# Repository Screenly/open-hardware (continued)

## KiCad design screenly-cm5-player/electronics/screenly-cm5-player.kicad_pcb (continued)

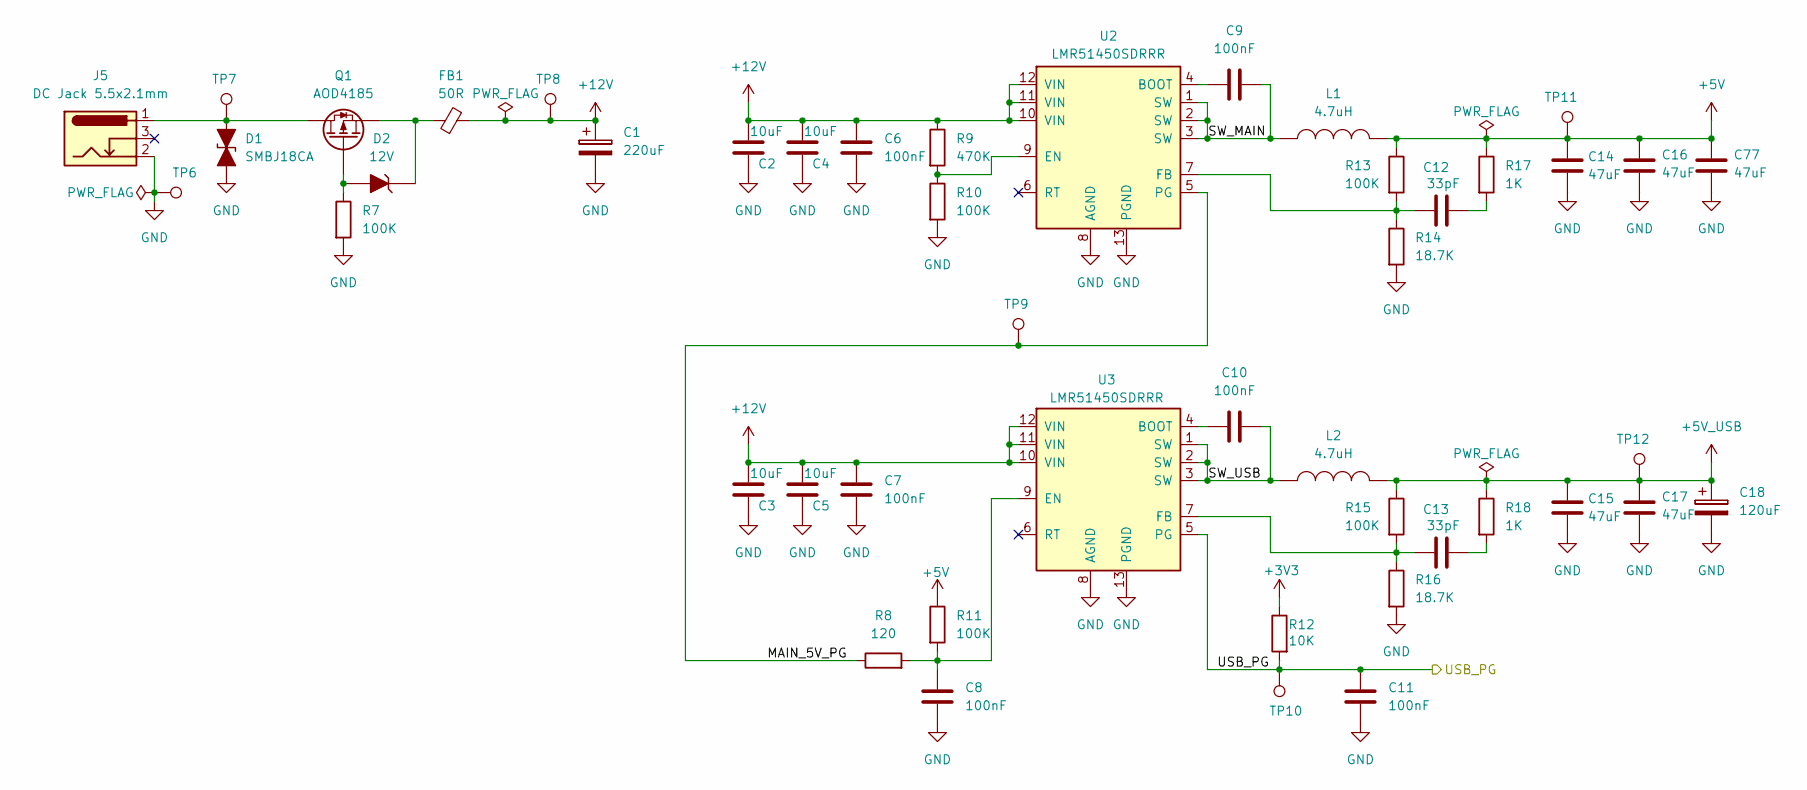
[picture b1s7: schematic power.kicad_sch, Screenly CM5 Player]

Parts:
C1: 220uF; CP_Radial_D6.3mm_P2.50mm; tolerance 20%; voltage 35V; PartNumber SRLY-CAP-000008
C2, C3, C4, C5: 10uF; C_1210; tolerance 10%; voltage 50V; PartNumber SRLY-CAP-000002
C6, C7, C8, C9, C10, C11: 100nF; C_0402; tolerance 10%; voltage 50V; PartNumber SRLY-CAP-000001
C12, C13: 33pF; C_0402; tolerance 5%; voltage 50V; PartNumber SRLY-CAP-000003
C14, C15, C16, C17, C77: 47uF; C_1210; tolerance 10%; voltage 10V; PartNumber SRLY-CAP-000005
C18: 120uF; CP_Elec_6.3x5.9; tolerance 20%; voltage 10V; PartNumber SRLY-CAP-000006
D1: SMBJ18CA; D_SMB; PartNumber SRLY-DIO-000001
D2: 12V; D_SOD-123; tolerance 6%; PartNumber SRLY-DIO-000002
FB1: 50R; FB_1206; PartNumber SRLY-FBD-000001
J5: DC Jack 5.5x2.1mm; BarrelJack_Tensility_54-00129_Horizontal; voltage 57V; PartNumber SRLY-CON-000004
L1, L2: 4.7uH; L_Coilank_AAPS1050; tolerance 20%; PartNumber SRLY-IND-000001
Q1: AOD4185; TO-252-2; PartNumber SRLY-FET-000001
R7, R10, R11, R13, R15: 100K; R_0402; tolerance 1%; voltage 50V; PartNumber SRLY-RES-000004
R8: 120; R_0402; tolerance 5%; voltage 50V; PartNumber SRLY-RES-000009
R9: 470K; R_0402; tolerance 5%; voltage 50V; PartNumber SRLY-RES-000003
R12: 10K; R_0402; tolerance 1%; voltage 50V; PartNumber SRLY-RES-000005
R14, R16: 18.7K; R_0402; tolerance 1%; voltage 50V; PartNumber SRLY-RES-000016
R17, R18: 1K; R_0402; tolerance 5%; voltage 50V; PartNumber SRLY-RES-000006
TP6, TP7, TP8, TP9, TP10, TP11, TP12: TestPoint; TestPoint_Pad_D2.0mm
U2, U3: LMR51450SDRRR; TI_WSON-12-1EP_3x3mm_P0.5mm_EP1.3x2.5mm; PartNumber SRLY-PWR-000001

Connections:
+3V3: R12.1; also elsewhere on the board
+5V: C14.1, C16.1, C77.1, L1.2, R11.1, R13.1, R17.1, TP11.1 (1_1); also elsewhere on the board
+5V_USB: C15.1, C17.1, C18.1, L2.2, R15.1, R18.1, TP12.1 (1_1); also elsewhere on the board
+12V: C1.1, C2.1, C3.1, C4.1, C5.1, C6.1, C7.1, FB1.2, R9.1, TP8.1 (1_1), U2.10 (VIN), U2.11 (VIN), U2.12 (VIN), U3.10 (VIN), U3.11 (VIN), U3.12 (VIN); also elsewhere on the board
/Power/MAIN_5V_PG: R8.1, TP9.1 (1_1), U2.5 (PG)
/Power/SW_MAIN: C9.2, L1.1, U2.1 (SW), U2.2 (SW), U2.3 (SW)
/Power/SW_USB: C10.2, L2.1, U3.1 (SW), U3.2 (SW), U3.3 (SW)
/USB_PG: C11.2, R12.2, TP10.1 (1_1), U3.5 (PG); also elsewhere on the board
GND: C1.2, C2.2, C3.2, C4.2, C5.2, C6.2, C7.2, C8.1, C11.1, C14.2, C15.2, C16.2, C17.2, C18.2, C77.2, D1.2 (A2), J5.2, R7.2, R10.2, R14.2, R16.2, TP6.1 (1_1), U2.8 (AGND), U2.13 (PGND), U3.8 (AGND), U3.13 (PGND); also elsewhere on the board
unnamed: C12.2, R17.2
unnamed: C13.2, R18.2
unnamed: D1.1 (A1), J5.1, Q1.2 (D), TP7.1 (1_1)
unnamed: D2.2 (A), Q1.1 (G), R7.1
unnamed: D2.1 (K), FB1.1, Q1.3 (S)
unnamed: C9.1, U2.4 (BOOT)
unnamed: R9.2, R10.1, U2.9 (EN)
unnamed: C12.1, R13.2, R14.1, U2.7 (FB)
unnamed: C10.1, U3.4 (BOOT)
unnamed: C8.2, R8.2, R11.2, U3.9 (EN)
unnamed: C13.1, R15.2, R16.1, U3.7 (FB)

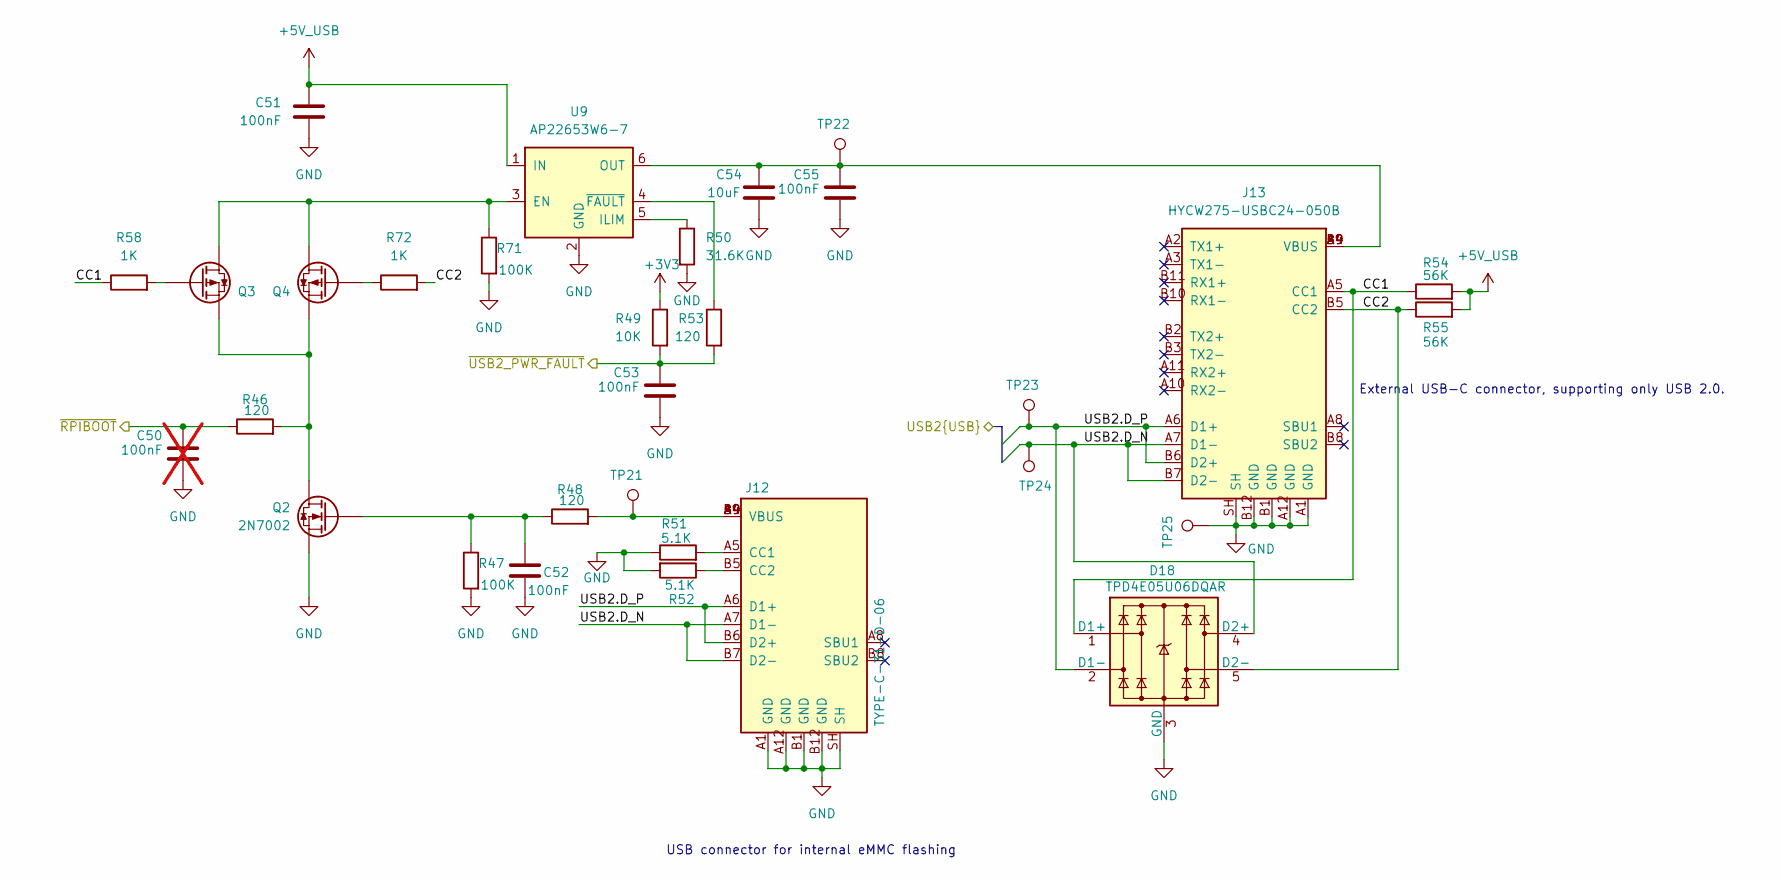
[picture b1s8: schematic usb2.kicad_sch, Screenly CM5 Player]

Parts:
C50: 100nF; C_0402; tolerance 10%; voltage 50V; PartNumber SRLY-CAP-000001; not fitted
C51, C52, C53, C55: 100nF; C_0402; tolerance 10%; voltage 50V; PartNumber SRLY-CAP-000001
C54: 10uF; C_1210; tolerance 10%; voltage 50V; PartNumber SRLY-CAP-000002
D18: TPD4E05U06DQAR; TI_USON-10_2.5x1.0mm_P0.5mm; PartNumber SRLY-DIO-000004
J12: TYPE-C-31-D-06; USB_C_Receptacle_HRO_TYPE-C-31-D-06_Vertical; voltage 5V; PartNumber SRLY-CON-000010
J13: HYCW275-USBC24-050B; USB_C_Receptacle_HOAUC_HYCW275-USBC24-050B; PartNumber SRLY-CON-000009
Q2: 2N7002; SOT-23; PartNumber SRLY-FET-000002
Q3, Q4: AO3401A; SOT-23; PartNumber SRLY-FET-000003
R46, R48, R53: 120; R_0402; tolerance 5%; voltage 50V; PartNumber SRLY-RES-000009
R47, R71: 100K; R_0402; tolerance 1%; voltage 50V; PartNumber SRLY-RES-000004
R49: 10K; R_0402; tolerance 1%; voltage 50V; PartNumber SRLY-RES-000005
R50: 31.6K; R_0402; tolerance 1%; voltage 50V; PartNumber SRLY-RES-000010
R51, R52: 5.1K; R_0402; tolerance 1%; voltage 50V; PartNumber SRLY-RES-000012
R54, R55: 56K; R_0402; tolerance 1%; voltage 50V; PartNumber SRLY-RES-000013
R58, R72: 1K; R_0402; tolerance 5%; voltage 50V; PartNumber SRLY-RES-000006
TP21, TP22, TP23, TP24, TP25: TestPoint; TestPoint_Pad_D2.0mm
U9: AP22653W6-7; SOT-23-6; PartNumber SRLY-PWR-000003

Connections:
+3V3: R49.1; also elsewhere on the board
+5V_USB: C51.1, R54.2, R55.2, U9.1 (IN); also elsewhere on the board
/Compute Module/USB2.D_N: D18.4 (D2+), D18.7, J12.A7 (D1-), J12.B7 (D2-), J13.A7 (D1-), J13.B7 (D2-), TP24.1 (1_1); also elsewhere on the board
/Compute Module/USB2.D_P: D18.2 (D1-), D18.9, J12.A6 (D1+), J12.B6 (D2+), J13.A6 (D1+), J13.B6 (D2+), TP23.1 (1_1); also elsewhere on the board
/Compute Module/~RPIBOOT: C50.1, R46.1; also elsewhere on the board
/Compute Module/~USB2_PWR_FAULT: C53.1, R49.2, R53.2; also elsewhere on the board
/USB2/CC1: D18.1 (D1+), D18.10, J13.A5 (CC1), R54.1, R58.1
/USB2/CC2: D18.5 (D2-), D18.6, J13.B5 (CC2), R55.1, R72.2
GND: C50.2, C51.2, C52.2, C53.2, C54.2, C55.2, D18.3 (GND), D18.8 (GND), J12.A1 (GND), J12.A12 (GND), J12.B1 (GND), J12.B12 (GND), J12.SH, J13.A1 (GND), J13.A12 (GND), J13.B1 (GND), J13.B12 (GND), J13.SH, Q2.2 (S), R47.2, R50.2, R51.1, R52.2, R71.2, TP25.1 (1_1), U9.2 (GND); also elsewhere on the board
unnamed: J12.A5 (CC1), R51.2
unnamed: J12.B5 (CC2), R52.1
unnamed: J12.A4 (VBUS), J12.A9 (VBUS), J12.B4 (VBUS), J12.B9 (VBUS), R48.2, TP21.1 (1_1)
unnamed: Q2.3 (D), Q3.2 (S), Q4.2 (S), R46.2
unnamed: C52.1, Q2.1 (G), R47.1, R48.1
unnamed: Q3.3 (D), Q4.3 (D), R71.1, U9.3 (EN)
unnamed: Q3.1 (G), R58.2
unnamed: Q4.1 (G), R72.1
unnamed: R50.1, U9.5 (ILIM)
unnamed: C54.1, C55.1, J13.A4 (VBUS), J13.A9 (VBUS), J13.B4 (VBUS), J13.B9 (VBUS), TP22.1 (1_1), U9.6 (OUT)
unnamed: R53.1, U9.4 (~FAULT)

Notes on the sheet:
External USB-C connector, supporting only USB 2.0.
USB connector for internal eMMC flashing

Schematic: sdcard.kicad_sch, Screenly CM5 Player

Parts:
C60, C61: 100nF; C_0402; tolerance 10%; voltage 50V; PartNumber SRLY-CAP-000001
C62: 10uF; C_1210; tolerance 10%; voltage 50V; PartNumber SRLY-CAP-000002
J14: 0472192001; microSD_HC_Molex_47219-2001; PartNumber SRLY-CON-000012
R62: 120; R_0402; tolerance 10%; voltage 50V; PartNumber SRLY-RES-000009
R63: 10K; R_0402; tolerance 1%; voltage 50V; PartNumber SRLY-RES-000005
R64: 47K; R_0402; tolerance 1%; voltage 50V; PartNumber SRLY-RES-000015
TP26: TestPoint; TestPoint_Pad_D2.0mm
U11: AP22653W6-7; SOT-23-6; PartNumber SRLY-PWR-000003

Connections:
+3V3: C60.1, R63.1, U11.1 (IN); also elsewhere on the board
/Compute Module/SD_CARD.CLK: J14.5 (CLK); also elsewhere on the board
/Compute Module/SD_CARD.CMD: J14.3 (CMD); also elsewhere on the board
/Compute Module/SD_CARD.D0: J14.7 (DAT0); also elsewhere on the board
/Compute Module/SD_CARD.D1: J14.8 (DAT1); also elsewhere on the board
/Compute Module/SD_CARD.D2: J14.1 (DAT2); also elsewhere on the board
/Compute Module/SD_CARD.D3: J14.2 (DAT3/CD); also elsewhere on the board
/Compute Module/SD_CARD.PWR_ON: R62.1; also elsewhere on the board
GND: C60.2, C61.2, C62.2, J14.6 (VSS), J14.SH, R64.2, U11.2 (GND); also elsewhere on the board
unnamed: C61.1, C62.1, J14.4 (VDD), TP26.1 (1_1), U11.6 (OUT)
unnamed: R62.2, R63.2, U11.3 (EN)
unnamed: R64.1, U11.5 (ILIM)

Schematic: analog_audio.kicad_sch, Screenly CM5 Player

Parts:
C64, C69, C70, C73: 100nF; C_0402; tolerance 10%; voltage 50V; PartNumber SRLY-CAP-000001
C65, C66, C67, C68: 10uF; C_1210; tolerance 10%; voltage 50V; PartNumber SRLY-CAP-000002
C71, C72: 2.2uF; C_0603; tolerance 10%; voltage 16V; PartNumber SRLY-CAP-000009
C74, C75: 2.2nF; C_0402; tolerance 5%; voltage 50V; PartNumber SRLY-CAP-000010
D17: PESD5V0U2BT; SOT-23; PartNumber SRLY-DIO-000005
J15: PJ-320A-4P; Jack_3.5mm_SHOUHAN_PJ-320A-4P_Horizontal; voltage 30V; PartNumber SRLY-CON-000013
R68: 10K; R_0402; tolerance 1%; voltage 50V; PartNumber SRLY-RES-000005
R69, R70: 470; R_0402; tolerance 5%; voltage 50V; PartNumber SRLY-RES-000001
U13: PCM5102APWR; TSSOP-20_4.4x6.5mm_P0.65mm; PartNumber SRLY-ITC-000003

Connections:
+3V3: C64.1, C65.1, C66.1, C68.1, C69.1, C73.1, R68.1, U13.1 (CPVDD), U13.8 (AVDD), U13.20 (DVDD); also elsewhere on the board
/Analog Audio/Audio.SCLK: U13.13 (BCK); also elsewhere on the board
/Analog Audio/Audio.SDO0: U13.14 (DIN); also elsewhere on the board
/Analog Audio/Audio.WS: U13.15 (LRCK); also elsewhere on the board
GND: C64.2, C65.2, C66.2, C67.2, C68.2, C69.2, C70.2, C72.2, C73.2, C74.1, C75.2, D17.3 (GND), J15.A (S), J15.B (R2), U13.3 (CPGND), U13.9 (AGND), U13.10 (DEMP), U13.11 (FLT), U13.12 (SCK), U13.16 (FMT), U13.19 (DGND); also elsewhere on the board
unnamed: C74.2, D17.1 (IO1), J15.D (T), R69.2
unnamed: C75.1, D17.2 (IO2), J15.C (R1), R70.2
unnamed: C71.2, U13.4 (CAPM)
unnamed: C71.1, U13.2 (CAPP)
unnamed: C67.1, C70.1, U13.18 (LDOO)
unnamed: R69.1, U13.6 (OUTL)
unnamed: R70.1, U13.7 (OUTR)
unnamed: C72.1, U13.5 (VNEG)
unnamed: R68.2, U13.17 (XSMT)

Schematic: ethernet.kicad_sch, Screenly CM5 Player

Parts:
C19: 100nF; C_0402; tolerance 10%; voltage 50V; PartNumber SRLY-CAP-000001
D3, D4: TPD4E05U06DQAR; TI_USON-10_2.5x1.0mm_P0.5mm; PartNumber SRLY-DIO-000004
J6: HB-W01G0520DQW-R; RJ45_Hanbo_HB-W01G0520DQW-R_Horizontal; PartNumber SRLY-CON-000005
R19, R20: 470; R_0402; tolerance 5%; voltage 50V; PartNumber SRLY-RES-000001

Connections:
+3V3: J6.L1 (LED_GRN_A), J6.L4 (LED_YEL_A); also elsewhere on the board
/Compute Module/ETH.TRD0_N: D3.2 (D1-), D3.9, J6.3 (TD1-); also elsewhere on the board
/Compute Module/ETH.TRD0_P: D3.1 (D1+), D3.10, J6.2 (TD1+); also elsewhere on the board
/Compute Module/ETH.TRD1_N: D3.4 (D2+), D3.7, J6.7 (TD2-); also elsewhere on the board
/Compute Module/ETH.TRD1_P: D3.5 (D2-), D3.6, J6.4 (TD2+); also elsewhere on the board
/Compute Module/ETH.TRD2_N: D4.2 (D1-), D4.9, J6.6 (TD3-); also elsewhere on the board
/Compute Module/ETH.TRD2_P: D4.1 (D1+), D4.10, J6.5 (TD3+); also elsewhere on the board
/Compute Module/ETH.TRD3_N: D4.4 (D2+), D4.7, J6.9 (TD4-); also elsewhere on the board
/Compute Module/ETH.TRD3_P: D4.5 (D2-), D4.6, J6.8 (TD4+); also elsewhere on the board
/Compute Module/~ETH_LED_ACT: R20.2; also elsewhere on the board
/Compute Module/~ETH_LED_SPD: R19.2; also elsewhere on the board
GND: C19.2, D3.3 (GND), D3.8 (GND), D4.3 (GND), D4.8 (GND), J6.10 (CAP_GND), J6.SH (SHIELD); also elsewhere on the board
unnamed: C19.1, J6.1 (CT)
unnamed: J6.L2 (LED_GRN_K), R20.1
unnamed: J6.L3 (LED_YEL_K), R19.1

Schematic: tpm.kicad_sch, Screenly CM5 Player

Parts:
C56, C57, C58, C76: 100nF; C_0402; tolerance 10%; voltage 50V; PartNumber SRLY-CAP-000001
C59: 1uF; C_0402; tolerance 10%; voltage 25V; PartNumber SRLY-CAP-000007
R56, R57: 10K; R_0402; tolerance 1%; voltage 50V; PartNumber SRLY-RES-000005
R59, R60, R61: 33R; R_0402; tolerance 5%; voltage 50V; PartNumber SRLY-RES-000014
U10: SLB9672XU20FW1624; Infineon_PG-UQFN-32-1_5x5mm_P0.5mm_EP3.6x3.6mm; PartNumber SRLY-ITC-000002

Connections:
+3V3: C56.1, C57.1, C58.1, C59.1, R56.1, R57.1, U10.1 (VDD), U10.8 (NCI/VDD), U10.14 (VDD), U10.22 (VDD); also elsewhere on the board
/Compute Module/TPM.CLK: R59.1; also elsewhere on the board
/Compute Module/TPM.MISO: R61.1; also elsewhere on the board
/Compute Module/TPM.MOSI: R60.1; also elsewhere on the board
/Compute Module/TPM.~CS: R56.2, U10.20 (~CS); also elsewhere on the board
/Compute Module/~TPM_PIRQ: R57.2, U10.18 (~PIRQ); also elsewhere on the board
/Compute Module/~TPM_RST: C76.1, U10.17 (~RST); also elsewhere on the board
/TPM/TPM_CLK_F: R59.2, U10.19 (SCLK)
/TPM/TPM_MISO_F: R61.2, U10.24 (MISO)
/TPM/TPM_MOSI_F: R60.2, U10.21 (MOSI)
GND: C56.2, C57.2, C58.2, C59.2, C76.2, U10.2 (GND), U10.9 (GND), U10.16 (NCI/GND), U10.23 (GND), U10.32 (GND), U10.33 (GND); also elsewhere on the board

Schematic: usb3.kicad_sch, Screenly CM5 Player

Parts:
C38, C39, C40, C41, C42, C43, C46, C47: 100nF; C_0402; tolerance 10%; voltage 50V; PartNumber SRLY-CAP-000001
C44, C45: 10uF; C_1210; tolerance 10%; voltage 50V; PartNumber SRLY-CAP-000002
D11, D12, D13, D14: TPD4E05U06DQAR; TI_USON-10_2.5x1.0mm_P0.5mm; PartNumber SRLY-DIO-000004
J10, J11: USB-A3-S-RA; USB_A_USB3_AdamTech_USB-A3-S-RA_Horizontal; voltage 30V; PartNumber SRLY-CON-000011
R33, R34: 100K; R_0402; tolerance 1%; voltage 50V; PartNumber SRLY-RES-000004
R35, R36, R38: 10K; R_0402; tolerance 1%; voltage 50V; PartNumber SRLY-RES-000005
R37: 18.7K; R_0402; tolerance 1%; voltage 50V; PartNumber SRLY-RES-000016
R39, R40: 120; R_0402; tolerance 5%; voltage 50V; PartNumber SRLY-RES-000009
TP15, TP16: TestPoint; TestPoint_Pad_D2.0mm
U7, U8: AP22653W6-7; SOT-23-6; PartNumber SRLY-PWR-000003

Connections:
+3V3: R35.1, R36.1; also elsewhere on the board
+5V_USB: C38.1, C39.1, U7.1 (IN), U8.1 (IN); also elsewhere on the board
/Compute Module/USB3_0.D_N: D11.2 (D1-), D11.9, J10.2 (D-); also elsewhere on the board
/Compute Module/USB3_0.D_P: D11.1 (D1+), D11.10, J10.3 (D+); also elsewhere on the board
/Compute Module/USB3_0.RX_N: D13.4 (D2+), D13.7, J10.5 (SSRX-); also elsewhere on the board
/Compute Module/USB3_0.RX_P: D13.5 (D2-), D13.6, J10.6 (SSRX+); also elsewhere on the board
/Compute Module/USB3_0.TX_N: D11.4 (D2+), D11.7, J10.8 (SSTX-); also elsewhere on the board
/Compute Module/USB3_0.TX_P: D11.5 (D2-), D11.6, J10.9 (SSTX+); also elsewhere on the board
/Compute Module/USB3_1.D_N: D12.2 (D1-), D12.9, J11.2 (D-); also elsewhere on the board
/Compute Module/USB3_1.D_P: D12.1 (D1+), D12.10, J11.3 (D+); also elsewhere on the board
/Compute Module/USB3_1.RX_N: D14.5 (D2-), D14.6, J11.5 (SSRX-); also elsewhere on the board
/Compute Module/USB3_1.RX_P: D14.4 (D2+), D14.7, J11.6 (SSRX+); also elsewhere on the board
/Compute Module/USB3_1.TX_N: D12.4 (D2+), D12.7, J11.8 (SSTX-); also elsewhere on the board
/Compute Module/USB3_1.TX_P: D12.5 (D2-), D12.6, J11.9 (SSTX+); also elsewhere on the board
/Compute Module/VBUS_EN: C40.1, C41.1, R33.1, R34.1, U7.3 (EN), U8.3 (EN); also elsewhere on the board
/Compute Module/~USB3_0_PWR_FAULT: C42.1, R35.2, R39.2; also elsewhere on the board
/Compute Module/~USB3_1_PWR_FAULT: C43.1, R36.2, R40.2; also elsewhere on the board
GND: C38.2, C39.2, C40.2, C41.2, C42.2, C43.2, C44.2, C45.2, C46.2, C47.2, D11.3 (GND), D11.8 (GND), D12.3 (GND), D12.8 (GND), D13.3 (GND), D13.8 (GND), D14.3 (GND), D14.8 (GND), J10.4 (GND), J10.7 (GND_DRAIN), J10.SH, J11.4 (GND), J11.7 (GND_DRAIN), J11.SH, R33.2, R34.2, R37.2, R38.2, U7.2 (GND), U8.2 (GND); also elsewhere on the board
unnamed: C44.1, C46.1, J10.1 (VBUS), TP15.1 (1_1), U7.6 (OUT)
unnamed: C45.1, C47.1, J11.1 (VBUS), TP16.1 (1_1), U8.6 (OUT)
unnamed: R37.1, U7.5 (ILIM)
unnamed: R39.1, U7.4 (~FAULT)
unnamed: R38.1, U8.5 (ILIM)
unnamed: R40.1, U8.4 (~FAULT)

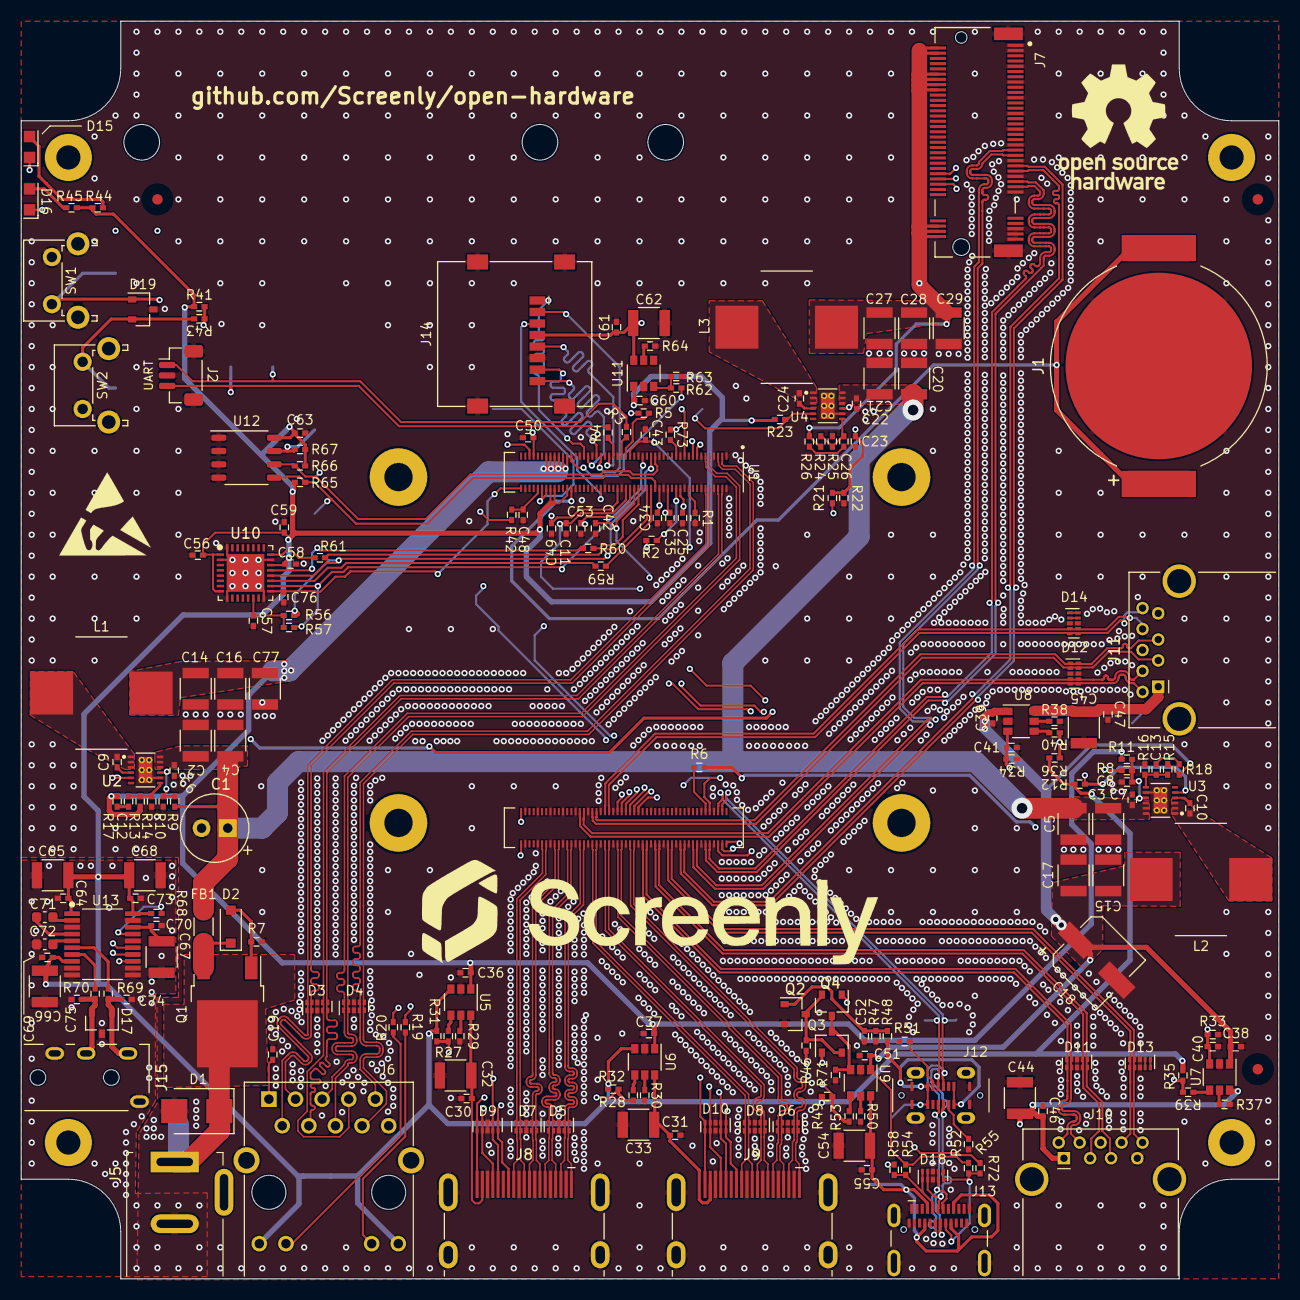
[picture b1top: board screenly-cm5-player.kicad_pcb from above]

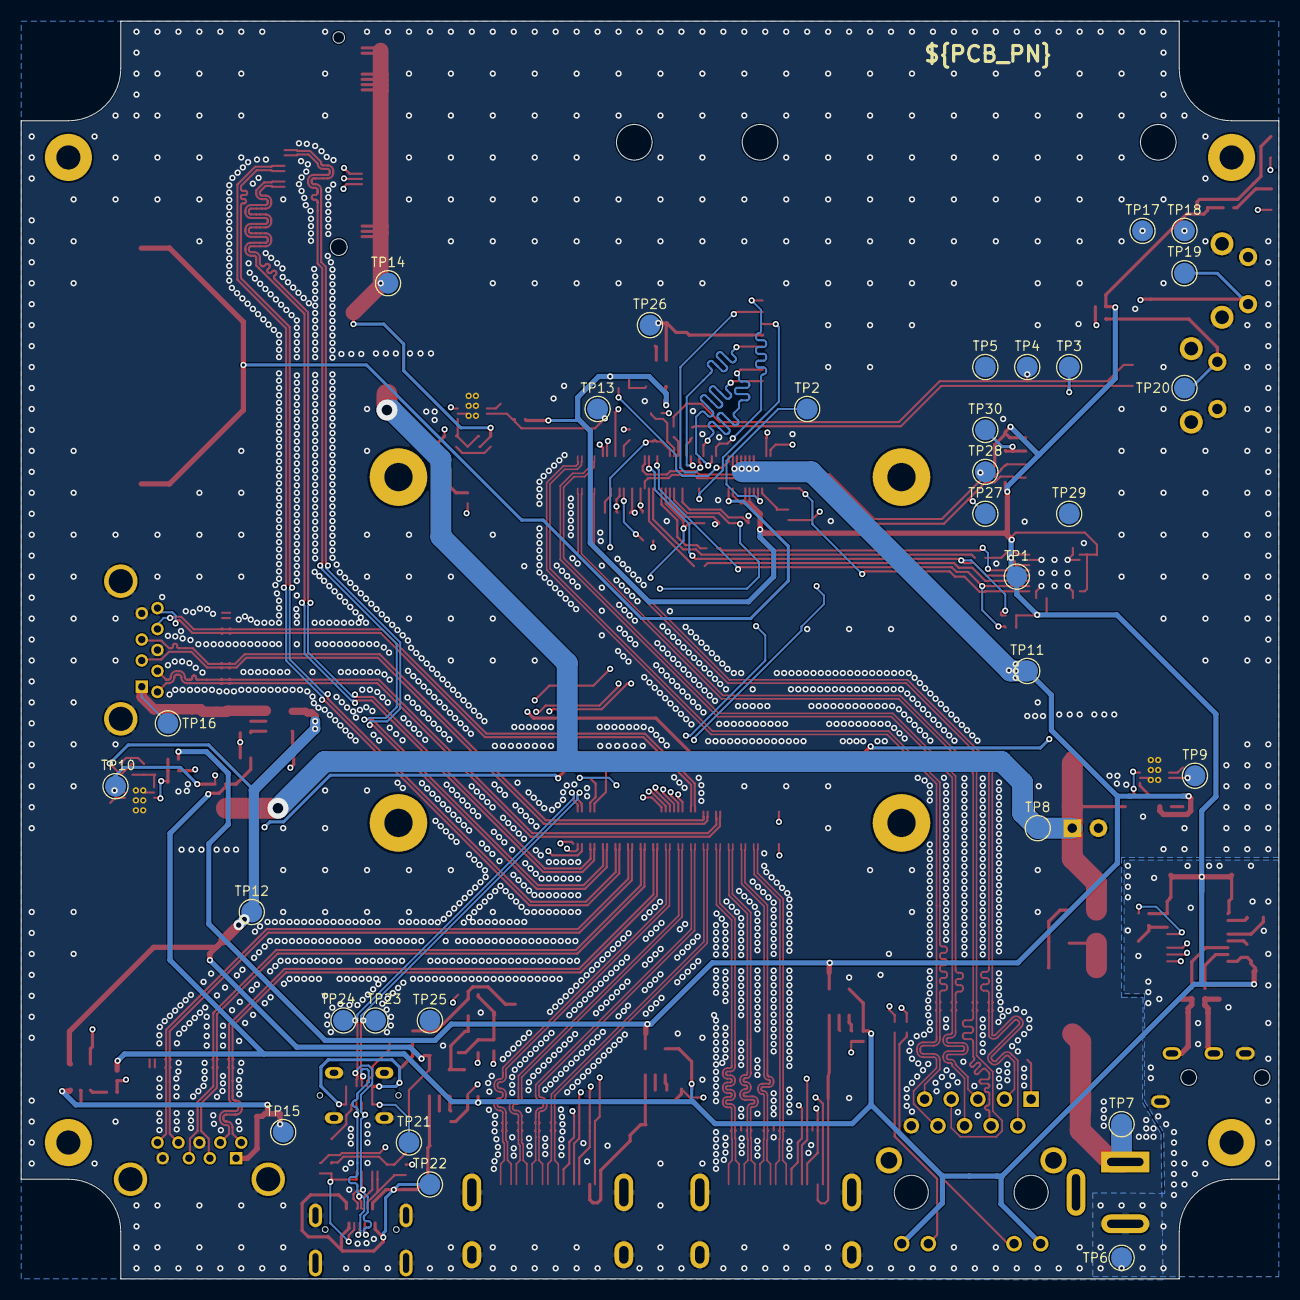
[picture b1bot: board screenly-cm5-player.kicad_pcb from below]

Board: 4 copper layers, 120.0 x 120.0 mm, 248 parts (30 on the bottom side), 173 nets.

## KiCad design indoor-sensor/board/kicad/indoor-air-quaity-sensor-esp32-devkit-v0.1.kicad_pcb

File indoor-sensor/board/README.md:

# Indoor Air Quality Sensor – XIAO ESP32S3 & CJMCU-6668

This repository contains the hardware design files for a compact Indoor Air Quality Sensor based on the Seeed Studio XIAO ESP32S3 and the CJMCU-6668 environmental sensor module (ENS160 + BME280).

## Main Components

| Part | Description |
|------|-------------|
| XIAO ESP32S3 | Primary MCU module (WiFi + BLE) |
| CJMCU-6668 | ENS160 + BME280 environmental sensor |
| I²C Pull-ups | 4.7kΩ resistors (if required) |
| Connector Headers | XIAO pin headers, sensor headers |
| Power Supply | USB-C (via XIAO) |
| Mounting Hardware | Optional standoffs and enclosure |

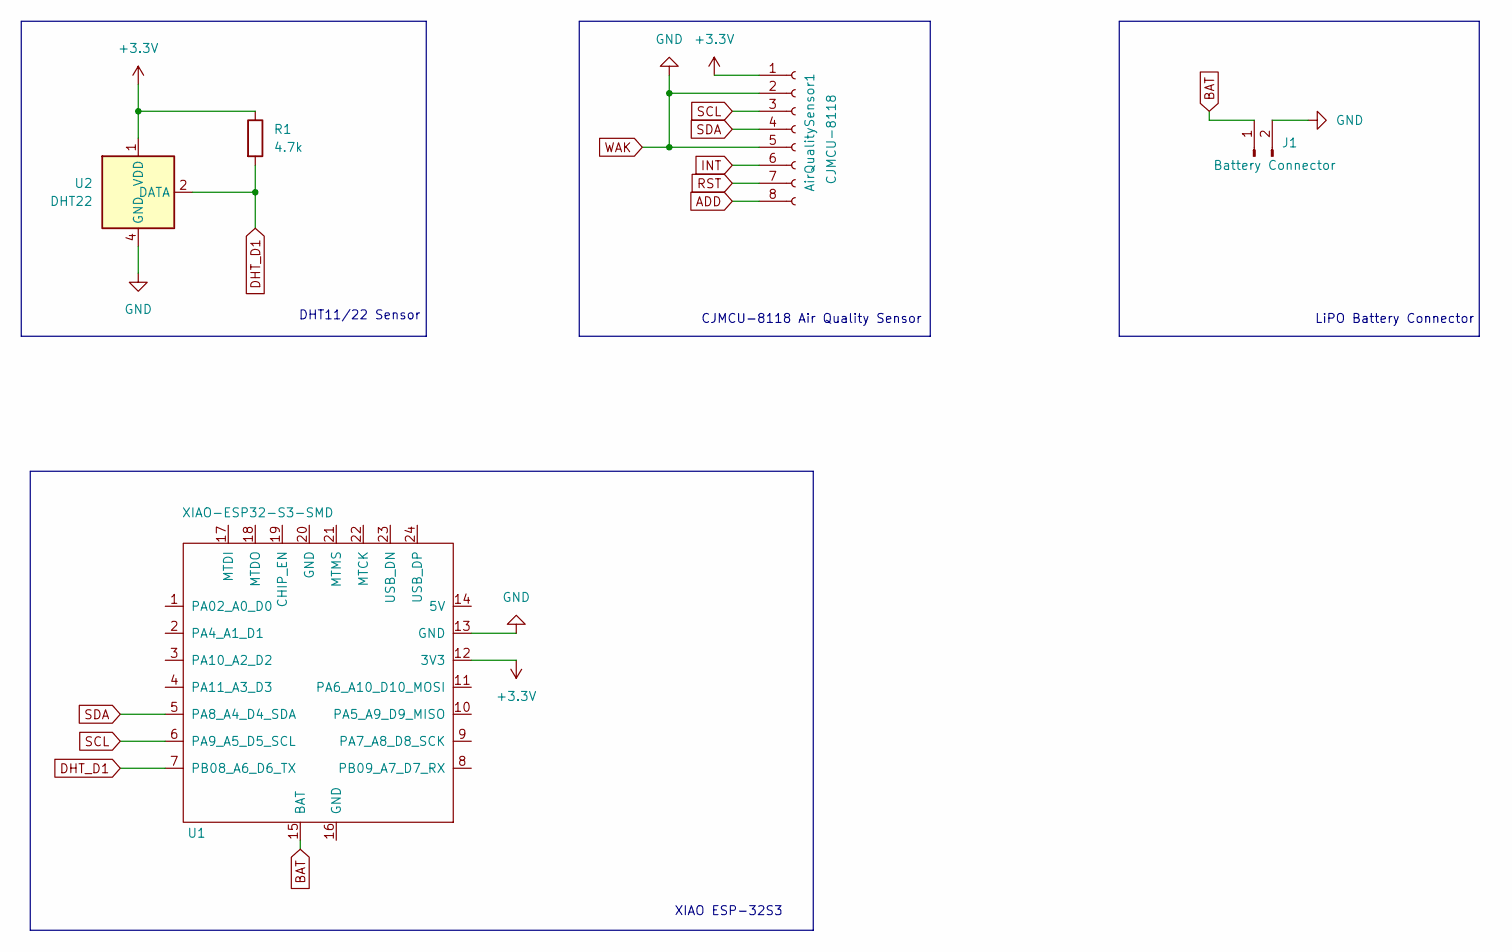
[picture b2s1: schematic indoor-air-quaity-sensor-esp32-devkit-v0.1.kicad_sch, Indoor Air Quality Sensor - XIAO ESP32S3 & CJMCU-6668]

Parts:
AirQualitySensor1: CJMCU-8118; PinHeader_1x08_P2.54mm_Vertical
J1: Battery Connector; PinHeader_1x02_P2.54mm_Vertical
R1: 4.7k; R_Axial_DIN0204_L3.6mm_D1.6mm_P5.08mm_Horizontal
U1: XIAO-ESP32-S3-SMD
U2: DHT22; Aosong_DHT11_5.5x12.0_P2.54mm

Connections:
+3.3V: AirQualitySensor1.1, R1.1, U1.12 (3V3), U2.1 (VDD)
ADD: AirQualitySensor1.8
BAT: J1.1, U1.15 (BAT)
DHT_D1: R1.2, U1.7 (PB08_A6_D6_TX), U2.2 (DATA)
INT: AirQualitySensor1.6
RST: AirQualitySensor1.7
SCL: AirQualitySensor1.3, U1.6 (PA9_A5_D5_SCL)
SDA: AirQualitySensor1.4, U1.5 (PA8_A4_D4_SDA)
WAK: AirQualitySensor1.2, AirQualitySensor1.5, J1.2, U1.13 (GND), U2.4 (GND)

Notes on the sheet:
DHT11/22 Sensor
XIAO ESP-32S3
CJMCU-8118 Air Quality Sensor
LiPO Battery Connector

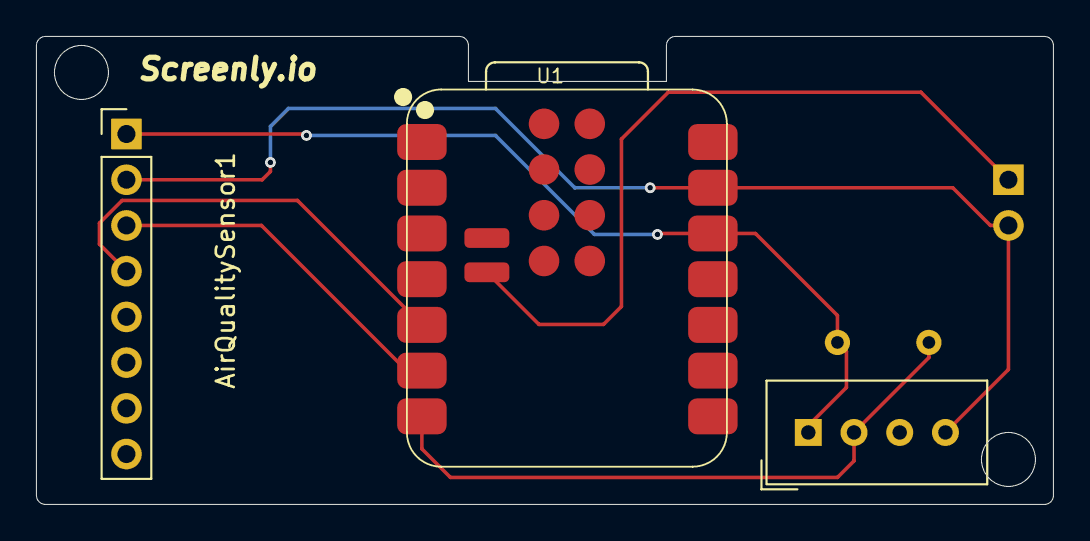
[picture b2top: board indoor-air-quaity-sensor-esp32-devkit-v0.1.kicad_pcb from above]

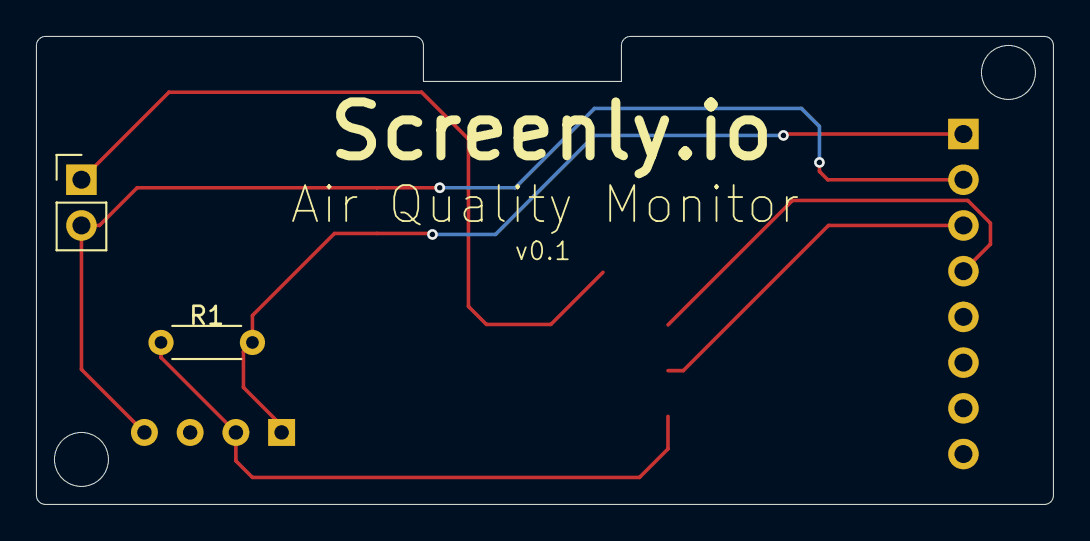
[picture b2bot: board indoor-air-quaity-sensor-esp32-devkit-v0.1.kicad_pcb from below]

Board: 2 copper layers, 56.5 x 26.0 mm, 5 parts (2 on the bottom side), 6 nets.

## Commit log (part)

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2025-05-05 Adds initial draft
2025-12-08 add kicad pcb files
